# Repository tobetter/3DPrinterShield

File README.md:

## 3D Printer Shield 

"3D Printer Shield" is a board to run 3D printer using ODROID single board
computer, technically this board is designed to control the motor driver
modules with TMC2209 (UART) or TMC2130 (SPI) through the on-board GPIO
headers without an additional processessor.

Originally this project is started to use RAMPS 1.6, but has changed to design
a new board since board connection is quite different.

The board has been tested with Ender-3 and runs by Klipper.

Then later, I've built an OS image to run Klipper on ODROID-C4 and the image
can be downloaded from [the link](https://bit.ly/3ppd9lL)

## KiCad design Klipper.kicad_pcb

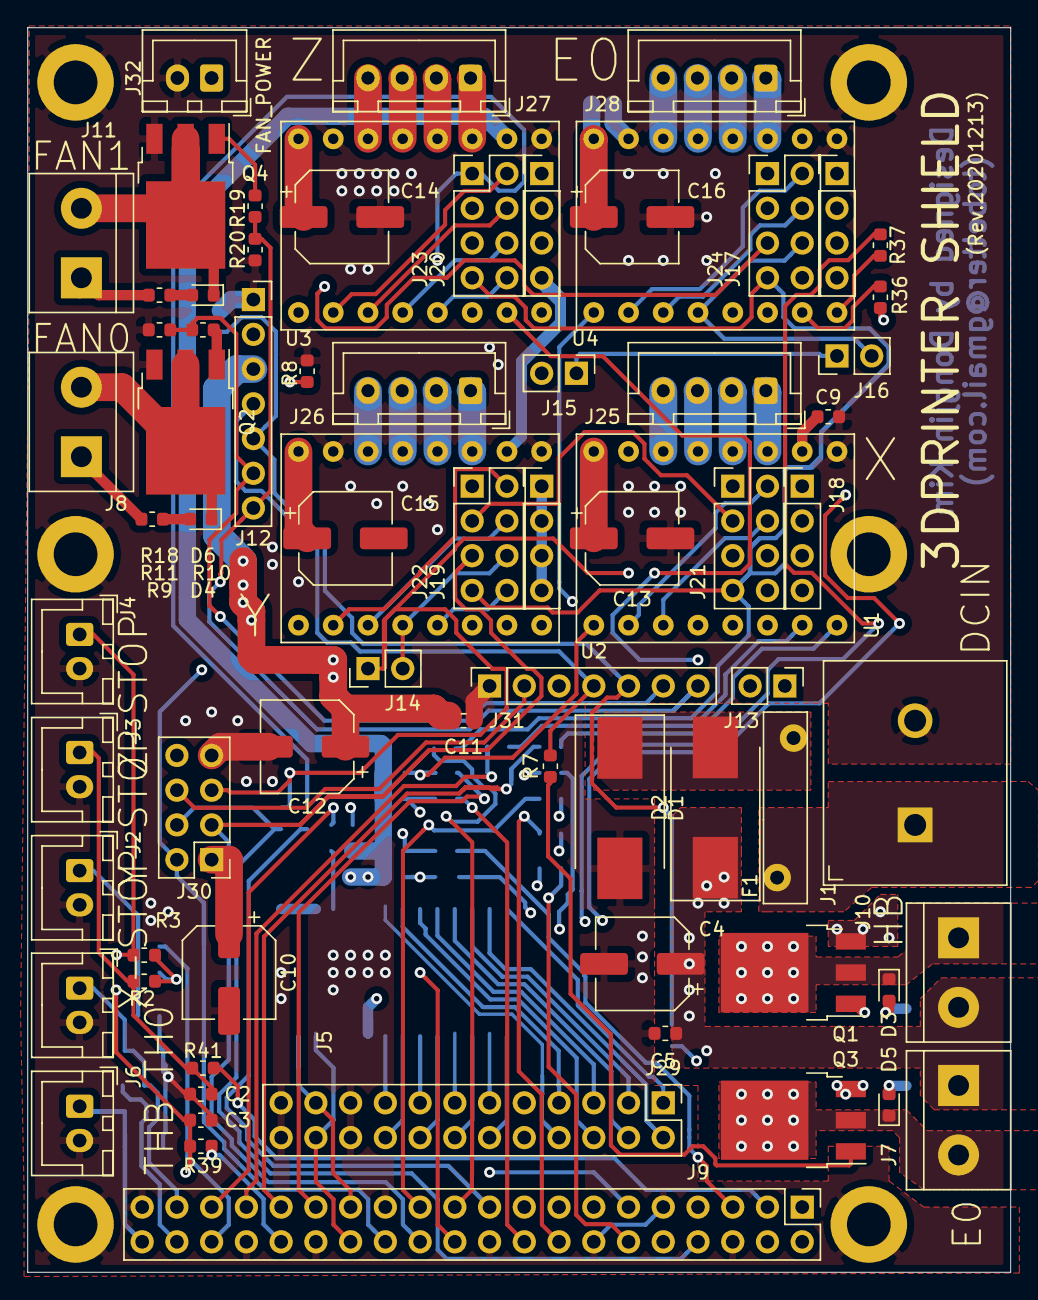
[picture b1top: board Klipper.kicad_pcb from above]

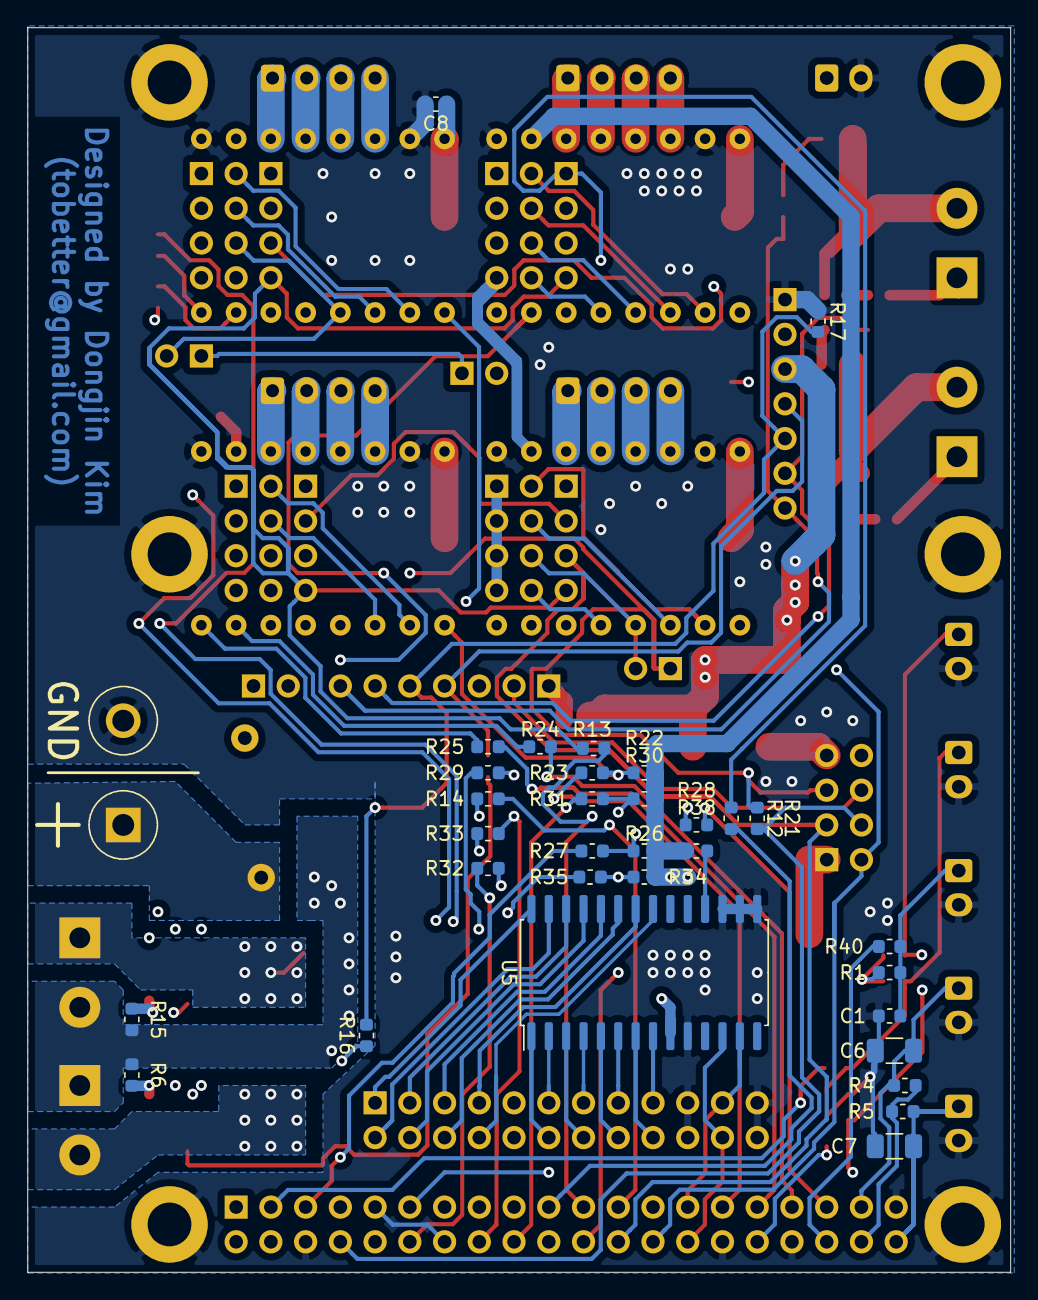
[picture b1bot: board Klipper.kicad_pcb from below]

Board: 4 copper layers, 71.9 x 91.0 mm, 111 parts (32 on the bottom side), 119 nets.

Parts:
C1, C2, C3, C5, C8, C9, C11: 0.1uF; C_0603_1608Metric
C4, C10, C12, C13, C14, C15, C16: 100uF/35V; CP_Elec_6.3x5.9
C6, C7: 10uF/10; C_1206_3216Metric
D1: S1D; D_SMC_Handsoldering
D2: SS54CF; D_SMC_Handsoldering
D3, D4, D5, D6: LED; LED_0603_1608Metric
F1: Fuse; FRU500-30F
H1, H2, H3, H4, H6, H7: MountingHole_Pad; MountingHole_3.2mm_M3_DIN965_Pad
J1: DCIN; TerminalBlock_BR_762C_P7.62mm
J2: X-STOP; JST_XH_B2B-XH-A_1x02_P2.50mm_Vertical
J3: Y-STOP; JST_XH_B2B-XH-A_1x02_P2.50mm_Vertical
J4: Z-STOP; JST_XH_B2B-XH-A_1x02_P2.50mm_Vertical
J5: TH0; JST_XH_B2B-XH-A_1x02_P2.50mm_Vertical
J6: THB; JST_XH_B2B-XH-A_1x02_P2.50mm_Vertical
J7: E0; TerminalBlock_bornier-2_P5.08mm
J8: FAN0; TerminalBlock_bornier-2_P5.08mm
J9: Conn_02x20_Odd_Even; PinHeader_2x20_P2.54mm_Vertical
J10: HB; TerminalBlock_bornier-2_P5.08mm
J11: FAN1; TerminalBlock_bornier-2_P5.08mm
J12, J31: Conn_01x07; PinSocket_1x07_P2.54mm_Vertical
J13, J14, J15, J16: Conn_01x02; PinHeader_1x02_P2.54mm_Vertical
J17, J18, J19, J20: Conn_01x04; PinHeader_1x04_P2.54mm_Vertical
J21, J22, J23, J24, J30: Conn_02x04_Odd_Even; PinHeader_2x04_P2.54mm_Vertical
J25: X; JST_XH_B4B-XH-A_1x04_P2.50mm_Vertical
J26: Y; JST_XH_B4B-XH-A_1x04_P2.50mm_Vertical
J27: Z; JST_XH_B4B-XH-A_1x04_P2.50mm_Vertical
J28: E0; JST_XH_B4B-XH-A_1x04_P2.50mm_Vertical
J29: Conn_02x12_Odd_Even; PinHeader_2x12_P2.54mm_Vertical
J32: FAN_POWER; JST_XH_B2B-XH-A_1x02_P2.50mm_Vertical
Q1, Q2, Q4: IRFR024N; TO-252-3_TabPin2
Q3: IRLR7843TRPBF; TO-252-3_TabPin2
R1, R2, R3, R38: 10K; R_0603_1608Metric
R4, R5, R6, R9, R15, R18: 4.7K; R_0603_1608Metric
R7, R10, R16, R19: 10; R_0603_1608Metric
R8, R11, R17, R20: 100k; R_0603_1608Metric
R12, R13, R14, R23, R24, R25, R27, R28, R29, R31, R32, R33, R35, R36, R37: 100; R_0603_1608Metric
R21, R39, R40, R41: 1k; R_0603_1608Metric
R22, R26, R30, R34: 10k; R_0603_1608Metric
U1: X; MOTOR_CARRIER
U2: Y; MOTOR_CARRIER
U3: Z; MOTOR_CARRIER
U4: E0; MOTOR_CARRIER
U5: MCP23017_SO; SOIC-28W_7.5x17.9mm_P1.27mm

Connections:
+1V8: J9.38, R4.1, R5.1
+3V3: C9.1, C10.1, J9.1, J9.17, J17.1, J17.2, J17.3, J17.4, J18.1, J18.2, J18.3, J18.4, J19.1, J19.2, J19.3, J19.4, J20.1, J20.2, J20.3, J20.4, J29.9, J29.10, J30.1, R1.1, R2.1, R3.1, R22.2, R26.2, R30.1, R34.2, R38.1, U1.10, U2.10, U3.10, U4.10, U5.9
+5V: C11.1, C12.1, J12.3, J31.3
/DCIN: F1.2, J1.1
/E0: J12.4, J31.4, R7.2, R8.2
/E0_CS: J12.2, J24.5, J30.6, J31.2
/E0_DIR: J9.13, R37.2
/E0_EN: J9.11, R35.2
/E0_MS3: J16.2, J24.6, U4.4
/E0_STEP: J9.15, R36.2
/FAN0: J12.6, J31.6, R10.2, R11.2
/FAN1: J12.7, J31.7, R19.2, R20.2
/FAN_POWER: J8.1, J11.1, J32.1, R9.1, R18.1
/GPA0: J29.8, U5.21
/GPA1: J29.7, U5.22
/GPA2: J29.6, U5.23
/GPA3: J29.5, U5.24
/GPA4: J29.4, U5.25
/GPA5: J29.3, U5.26
/GPA6: J29.2, U5.27
/GPA7: J29.1, U5.28
/GPB0: J29.12, U5.1
/GPB1: J29.11, U5.2
/GPB2: J29.14, U5.3
/GPB3: J29.13, U5.4
/GPB4: J29.16, U5.5
/GPB5: J29.15, U5.6
/GPB6: J29.18, U5.7
/GPB7: J29.17, U5.8
/HB: J12.5, J31.5, R16.2, R17.2
/MISO: J21.7, J22.7, J23.7, J24.7, R13.2
/MOSI: J21.1, J22.1, J23.1, J24.1, R12.2
/RX: J9.10, J13.1, J14.1, J15.1, J16.1, J30.5, R21.2
/SCL: J9.28, J29.22, U5.12
/SCLK: J21.3, J22.3, J23.3, J24.3, R14.2
/SDA: J9.27, J29.21, U5.13
/TH0: C6.1, J5.1, J9.37, R4.2
/TH1: C7.1, J6.1, J9.40, R5.2
/TX: J9.8, J30.4, R21.1
/X_CS: J9.22, J21.5, J30.8
/X_DIR: J9.31, R25.2
/X_EN: J9.29, R23.2
/X_MIN: J9.36, R40.1
/X_MS3: J13.2, J21.6, U1.4
/X_STEP: J9.33, R24.2
/Y_CS: J9.24, J22.5, J30.3
/Y_DIR: J9.7, R29.2
/Y_EN: J9.5, R27.2
/Y_MIN: J9.3, R41.1
/Y_MS3: J14.2, J22.6, U2.4
/Y_STEP: J9.35, R28.2
/Z_CS: J9.26, J23.5, J30.2
/Z_DIR: J9.16, R33.2
/Z_EN: J9.18, R31.2
/Z_MIN: J9.32, R39.1
/Z_MS3: J15.2, J23.6, U3.4
/Z_STEP: J9.12, R32.2
GNDPWR: C1.2, C2.2, C3.2, C4.2, C5.2, C6.2, C7.2, C8.2, C9.2, C10.2, C11.2, C12.2, C13.2, C14.2, C16.2, D1.2, H1.1, H2.1, H3.1, H4.1, H6.1, H7.1, J1.2, J2.2, J3.2, J4.2, J5.2, J6.2, J9.6, J9.9, J9.14, J9.20, J9.25, J9.30, J9.34, J9.39, J12.1, J29.19, J29.20, J29.23, J29.24, J30.7, J31.1, J32.2, Q1.3, Q2.3, Q3.3, Q4.3, R8.1, R11.1, R17.1, R20.1, U1.9, U1.15, U2.9, U2.15, U3.9, U3.15, U4.9, U4.15, U5.10, U5.15, U5.16, U5.17
unnamed: C1.1, J2.1, R1.2, R40.2
unnamed: C2.1, J3.1, R2.2, R41.2
unnamed: C3.1, J4.1, R3.2, R39.2
unnamed: D1.1, D2.2, F1.1
unnamed: D3.1, J10.1, Q1.2
unnamed: D3.2, R15.2
unnamed: D4.1, J8.2, Q2.2
unnamed: D4.2, R9.2
unnamed: D5.1, J7.2, Q3.2
unnamed: D5.2, R6.2
unnamed: D6.1, J11.2, Q4.2
unnamed: D6.2, R18.2
unnamed: J9.19, R12.1
unnamed: J9.21, R13.1
unnamed: J9.23, R14.1
unnamed: J21.2, U1.2
unnamed: J21.4, U1.3
unnamed: J21.8, U1.5
unnamed: J22.2, U2.2
unnamed: J22.4, U2.3
unnamed: J22.8, U2.5
unnamed: J23.2, U3.2
unnamed: J23.4, U3.3
unnamed: J23.8, U3.5
unnamed: J24.2, U4.2
unnamed: J24.4, U4.3
unnamed: J24.8, U4.5
unnamed: J25.1, U1.11
unnamed: J25.2, U1.12
unnamed: J25.3, U1.13
unnamed: J25.4, U1.14
unnamed: J26.1, U2.11
unnamed: J26.2, U2.12
unnamed: J26.3, U2.13
unnamed: J26.4, U2.14
unnamed: J27.1, U3.11
unnamed: J27.2, U3.12
unnamed: J27.3, U3.13
unnamed: J27.4, U3.14
unnamed: J28.1, U4.11
unnamed: J28.2, U4.12
unnamed: J28.3, U4.13
unnamed: J28.4, U4.14
unnamed: Q1.1, R16.1
unnamed: Q2.1, R10.1
unnamed: Q3.1, R7.1
unnamed: Q4.1, R19.1
unnamed: R22.1, R23.1, U1.1
unnamed: R24.1, U1.7
unnamed: R25.1, U1.8
unnamed: R26.1, R27.1, U2.1
unnamed: R28.1, U2.7
unnamed: R29.1, U2.8
unnamed: R30.2, R31.1, U3.1
unnamed: R32.1, U3.7
unnamed: R33.1, U3.8
unnamed: R34.1, R35.1, U4.1
unnamed: R36.1, U4.7
unnamed: R37.1, U4.8
unnamed: R38.2, U5.18
Vdrive: C4.1, C5.1, C8.1, C13.1, C14.1, C15.1, C16.1, D2.1, J7.1, J10.2, R6.1, R15.1, U1.16, U2.16, U3.16, U4.16

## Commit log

2020-12-13 First commit for new design
2021-03-16 Add Gerber files
2021-03-16 Add schematic in PDF
2021-03-16 Adding README and images
2021-03-17 Create LICENSE
